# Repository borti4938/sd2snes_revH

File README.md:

### sd2snes Upgrade to Rev.H from earlier versions
---

This is an earlier project and not under development anymore. Documentation is rather simple.

Please don't write me for any support. Please reach out to community forums and use the knowledge and experiences there.

Best Regards, Peter

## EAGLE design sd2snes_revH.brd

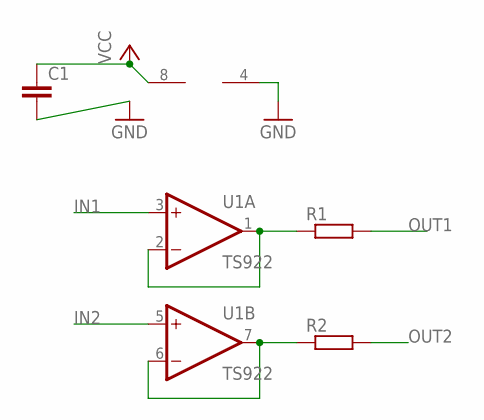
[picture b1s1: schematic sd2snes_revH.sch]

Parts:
C1: C-EUC0603; C0603
R1, R2: R-EU_R0603; R0603
U1: TS922; SO08

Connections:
GND: C1.2, U1.4 (V-)
IN1: U1.3 (+IN)
IN2: U1.5 (+IN)
unnamed: R1.1, U1.1 (OUT), U1.2 (-IN)
unnamed: R2.1, U1.6 (-IN), U1.7 (OUT)
OUT1: R1.2
OUT2: R2.2
VCC: C1.1, U1.8 (V+)

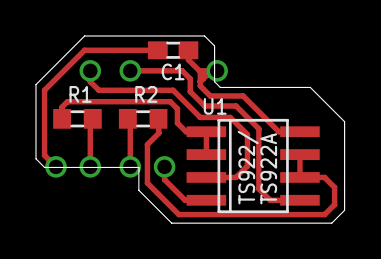
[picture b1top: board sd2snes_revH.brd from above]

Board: 2 copper layers, 17.1 x 10.4 mm, 4 parts (0 on the bottom side), 4 nets.

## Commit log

2020-05-03 initial commit for archive
